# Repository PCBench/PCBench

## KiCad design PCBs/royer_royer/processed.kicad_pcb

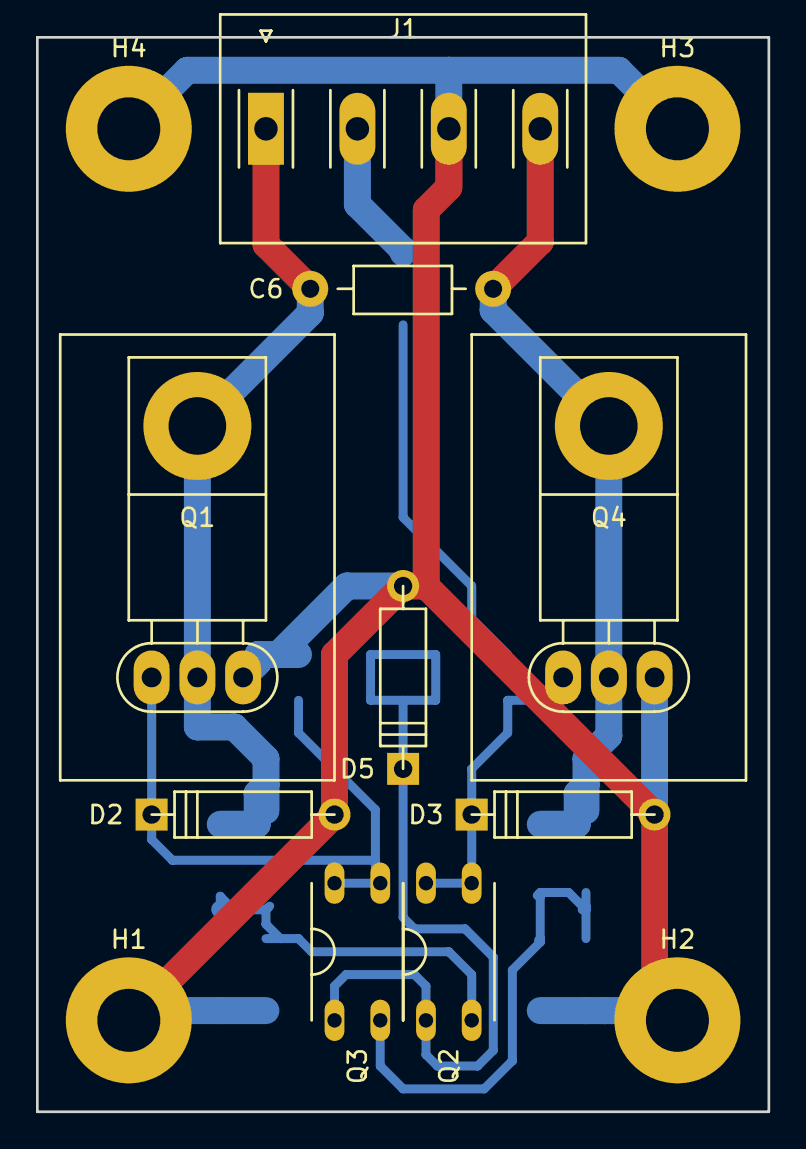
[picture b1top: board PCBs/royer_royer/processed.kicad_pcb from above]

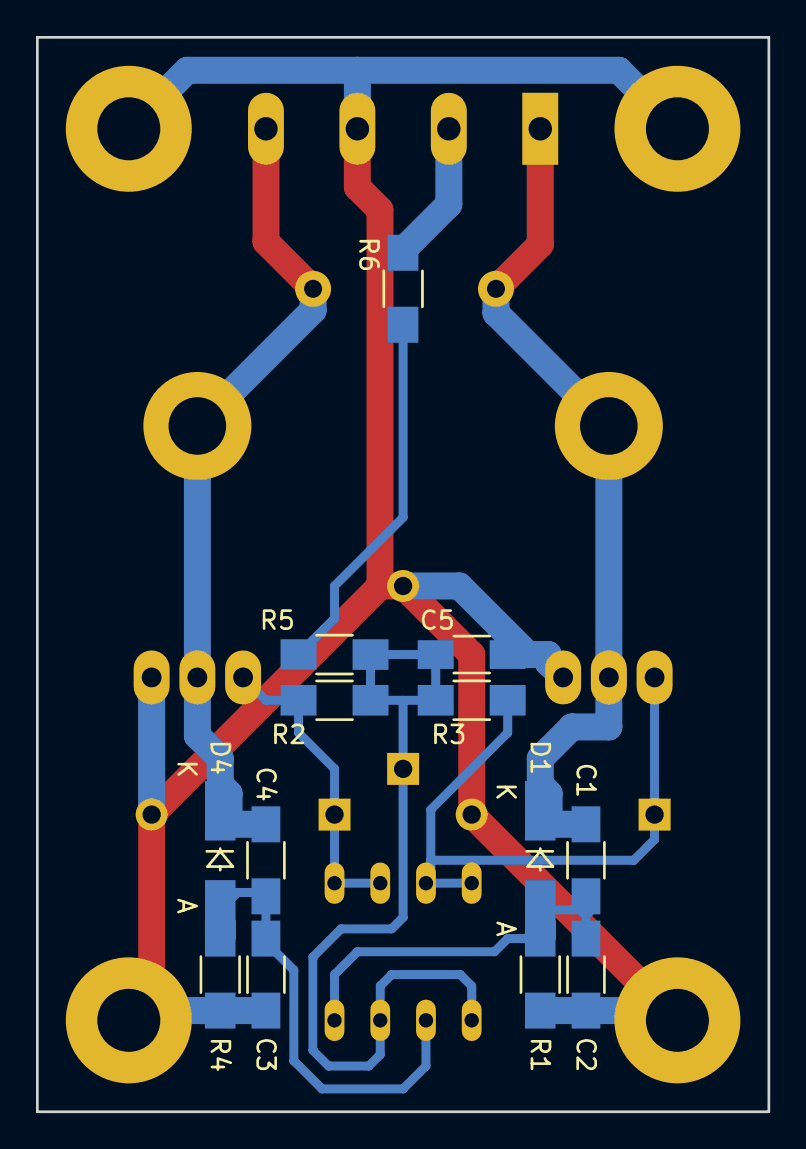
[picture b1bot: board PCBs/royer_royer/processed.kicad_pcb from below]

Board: 2 copper layers, 40.6 x 59.7 mm, 26 parts (13 on the bottom side), 10 nets.

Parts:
C1, C2, C3, C4: 10nF; C_1206_HandSoldering
C5: 470nF; C_1206_HandSoldering
C6: 1uF; Choke_Horizontal_RM10mm
D1, D4: 1N4148; MiniMELF_Handsoldering
D2, D3, D5: 9.1V; D4
H1, H2, H3, H4: 3.5mm; MountingHole_3.5mm_Pad
J1: Screw_Terminal_1x04; screw-terminal-4-pin
Q1, Q4: IRFB4410; TO-220-small-heatsink
Q2, Q3: IRFD110; DIP-4_W7.62mm_LongPads
R1, R4: 33k; R_1206_HandSoldering
R2, R3: 47k; R_1206_HandSoldering
R5, R6: 1k; R_1206_HandSoldering

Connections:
/9V: C5.1, D5.1, Q2.1, Q3.1, R2.1, R3.1, R5.2
/24V: J1.2, R6.1
/C1: C1.2, C6.2, D1.1, J1.1, Q1.2
/C2: C4.2, C6.1, D4.1, J1.4, Q4.2
/D1: C1.1, C2.1, D1.2, Q2.2, R1.1
/D2: C3.1, C4.1, D4.2, Q3.2, R4.1
/G1: D2.1, Q1.1, Q3.3, R3.2
/G2: D3.1, Q2.3, Q4.1, R2.2
GND: C2.2, C3.2, C5.2, D2.2, D3.2, D5.2, H1.1, H2.1, H3.1, H4.1, J1.3, Q1.3, Q4.3, R1.2, R4.2
unnamed: R5.1, R6.2

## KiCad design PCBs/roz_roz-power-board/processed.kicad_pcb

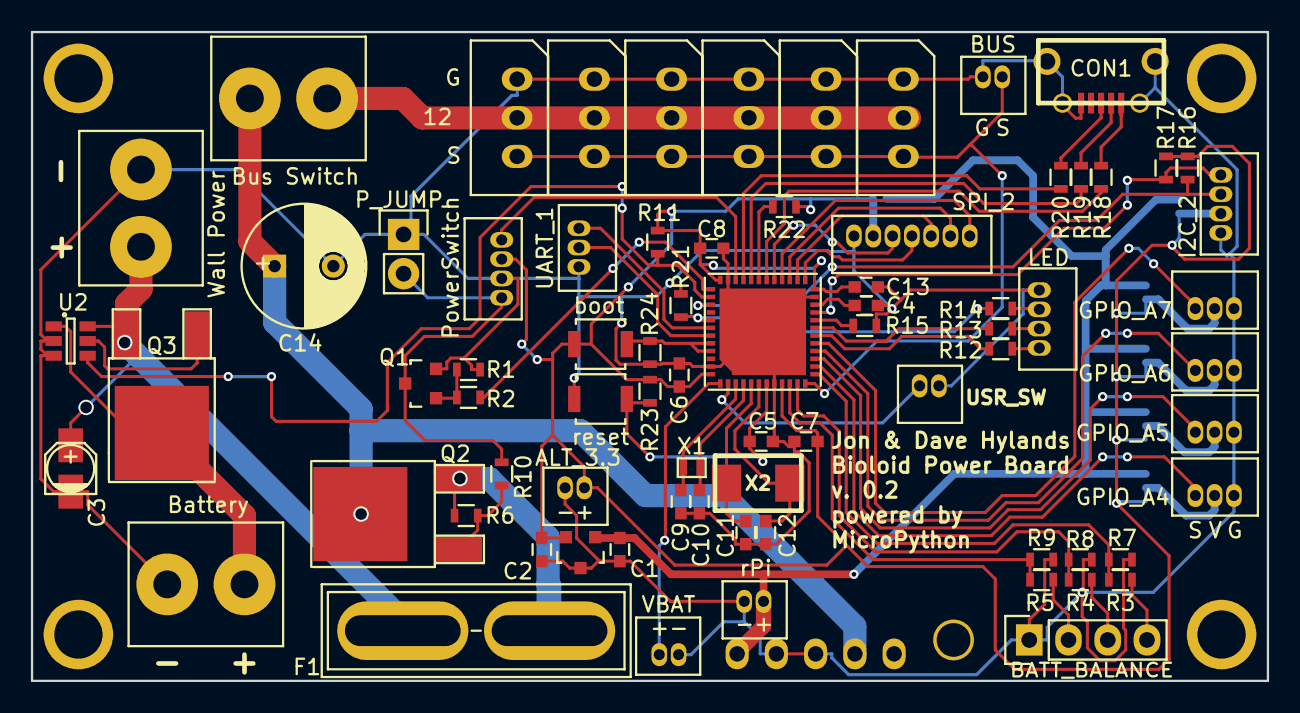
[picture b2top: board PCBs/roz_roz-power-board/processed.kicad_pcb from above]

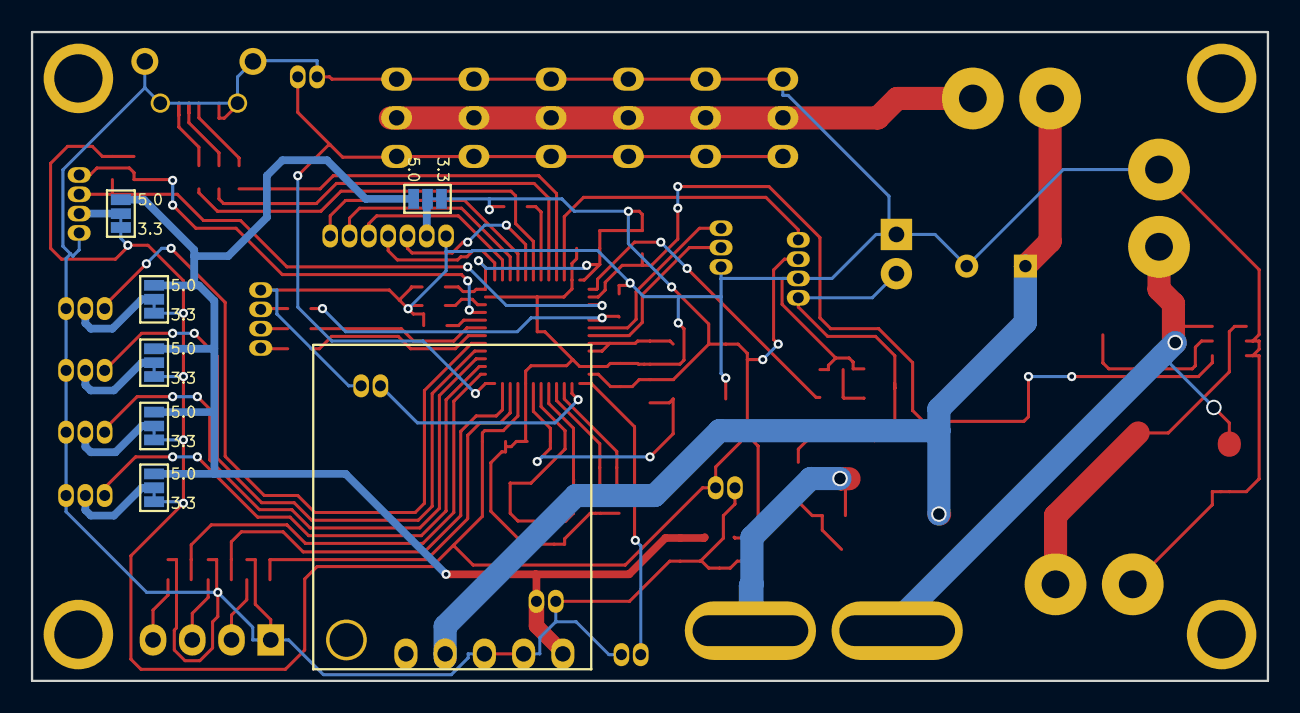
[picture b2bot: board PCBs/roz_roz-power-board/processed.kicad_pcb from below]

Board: 2 copper layers, 80.0 x 42.0 mm, 87 parts (7 on the bottom side), 64 nets.

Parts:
1PIN: P***; 2_56_hole
1PIN_2, 1PIN_3, 1PIN_4, 1PIN_5: P***; 4_40_hole
C1, C2, C4, C5, C6, C7, C8, C13: 0.1uF; C_0603
C3: 22uF; c_elec_3x5.3
C9, C10: 6pF; C_0603
C11, C12: 18pF; C_0603
C14: 680uF; C_Radial_D8_L21_P3.8
CON1: USB-MICRO-B; USB_MICRO_B
F1: FUSE; BladeFuse-CarType
J1, J2, J3, J4, J5, J6: Jumper_Switch; Jumper-Switch
P1: Wall Power; TerminalBlock
P2: Battery; TerminalBlock
P3: BATT_BALANCE; Socket_Strip_Straight_1x04
P4: ALT_3.3; SIL_2_050
P5: UART_1; SIL_3_050
P6: I2C_2; SIL_4_050
P7: SPI_2; SIL_7_050
P8: 5V Regulator; 5V_5A_VReg
P9: GPIO_A4; SIL_3_050
P10: GPIO_A5; SIL_3_050
P11: GPIO_A6; SIL_3_050
P12: GPIO_A7; SIL_3_050
P13: BIOLOID_BUS_1; Bioloid-3
P14: LED; SIL_4_050
P15: Bus Switch; TerminalBlock
P16: BIOLOID_BUS_2; Bioloid-3
P17: BIOLOID_BUS_3; Bioloid-3
P18: BIOLOID_BUS_4; Bioloid-3
P19: BIOLOID_BUS_5; Bioloid-3
P20: BIOLOID_BUS_6; Bioloid-3
P21: rPi; SIL_2_050
P23: USR_SW; SIL_2_050
P25: VBAT; SIL_2_050
P26: BUS; SIL_2_050
P_JUMP: P_JUMP; Socket_Strip_Straight_1x02
Q1: BS-170; SOT-23
Q2, Q3: STD30PF03LT4; TO-252-2Lead
R1, R10, R15, R21, R23: 10K; R_0603
R2: 100; R_0603
R3, R4, R5: 15K; R_0603
R6: 22K; R_0603
R7, R8, R9: 5K; R_0603
R11: 470K; R_0603
R12: 65; R_0603
R13: 0; R_0603
R14: 5; R_0603
R16, R17: 4.7K; R_0603
R18: 1K; R_0603
R19, R20: 20; R_0603
R22, R24: 100K; R_0603
SW2: PowerSwitch; SIL_4_050
SW3: RESET_SW; PUSH_SMT
SW4: BOOT_SW; PUSH_SMT
U1: AP7333; SOT-23
U2: LTC4412; SOT-23-6
U3: STM32F401xD_UFQFPN48; UFQFPN48
X1: 32.768kHz; CRYSTAL_SMT_3
X2: 8MHz; CRYSTAL_SMT

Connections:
+3V3: C2.1, C6.2, C7.2, C8.2, C13.2, J1.3, J2.3, J3.3, J4.3, J5.3, J6.3, P4.1, R11.2, R16.2, R17.2, R22.2, R23.1, SW2.3, SW4.2, U1.2, U3.9, U3.24, U3.36, U3.48
+5V: C1.1, J1.1, J2.1, J3.1, J4.1, J5.1, J6.1, P8.5, P21.1, U1.1
+12V: C14.1, P8.2, P15.2, Q2.2
+BATT: P2.2, Q3.2, U2.1
+F_POWER: F1.2, Q2.3, R6.2
+POWER: C3.1, F1.1, P1.2, Q3.3, U2.6
+SW_12V: P13.2, P15.1, P16.2, P17.2, P18.2, P19.2, P20.2
/OSC32_IN: C9.2, U3.3, X1.2
/OSC32_OUT: C10.2, U3.4, X1.1
/OSC_IN: C11.2, U3.5, X2.2
/OSC_OUT: C12.2, U3.6, X2.1
BIOLOID_TX: P13.1, P16.1, P17.1, P18.1, P19.1, P20.1, P26.1, U3.12
BOOT0: R24.2, SW4.1, U3.44, U3.45
CELL1_VOLTAGE: R5.1, R9.2, U3.10
CELL2_VOLTAGE: R4.1, R8.2, U3.11
CELL3_VOLTAGE: R3.1, R7.2, U3.13
GATE_PIN: R2.2, U3.37
GND: C1.2, C2.2, C3.2, C4.1, C5.1, C6.1, C7.1, C8.1, C9.1, C10.1, C11.1, C12.1, C13.1, C14.2, CON1.5, CON1.6, CON1.7, CON1.8, CON1.9, P1.1, P2.1, P3.1, P4.2, P5.3, P6.4, P7.7, P8.3, P8.4, P9.3, P10.3, P11.3, P12.3, P13.3, P14.1, P16.3, P17.3, P18.3, P19.3, P20.3, P21.2, P23.1, P25.2, P26.2, P_JUMP.1, Q1.2, R1.1, R7.1, R8.1, R9.1, R15.2, R21.2, R24.1, SW2.2, SW3.2, U1.3, U2.2, U2.3, U3.8, U3.23, U3.35, U3.47, U3.G1, U3.G2, U3.G3
GPIO_A4: P9.1, U3.14
GPIO_A5: P10.1, U3.15
GPIO_A6: P11.1, U3.16
GPIO_A7: P12.1, U3.17
I2C_2_SCL: P6.1, R17.1, U3.21
I2C_2_SDA: P6.2, R16.1, U3.39
LED_B: R14.1, R21.1, U3.41
LED_G: R13.1, U3.19
LED_R: R12.1, U3.18
unnamed: C4.2, U3.22
unnamed: C5.2, R23.2, SW3.1, U3.7
unnamed: CON1.1, R18.2
unnamed: CON1.2, R19.2
unnamed: CON1.3, R20.2
unnamed: J1.2, P6.3
unnamed: J2.2, P7.6
unnamed: J3.2, P9.2
unnamed: J4.2, P10.2
unnamed: J5.2, P11.2
unnamed: J6.2, P12.2
unnamed: P3.2, R5.2
unnamed: P3.3, R4.2
unnamed: P3.4, R3.2
unnamed: P14.2, R14.2
unnamed: P14.3, R13.2
unnamed: P14.4, R12.2
unnamed: P_JUMP.2, Q1.3, R10.1, SW2.1
unnamed: P23.2, U3.2
unnamed: Q1.1, R1.2, R2.1
unnamed: Q2.1, R6.1, R10.2
unnamed: Q3.1, U2.5
unnamed: R19.1, U3.32
unnamed: R20.1, U3.33
PA9: R18.1, U3.30
PA10: R22.1, U3.31
PB2: R15.1, U3.20
SPI_2_MISO: P7.2, U3.27
SPI_2_MOSI: P7.1, U3.28
SPI_2_SCK: P7.3, U3.26
SPI_CS_1: P7.4, U3.25
SPI_CS_2: P7.5, U3.29
STAT_PIN: R11.1, U2.4, U3.38
SWITCH_PIN: SW2.4, U3.34
UART_1_RX: P5.2, U3.43
UART_1_TX: P5.1, U3.42
VBAT: P25.1, U3.1

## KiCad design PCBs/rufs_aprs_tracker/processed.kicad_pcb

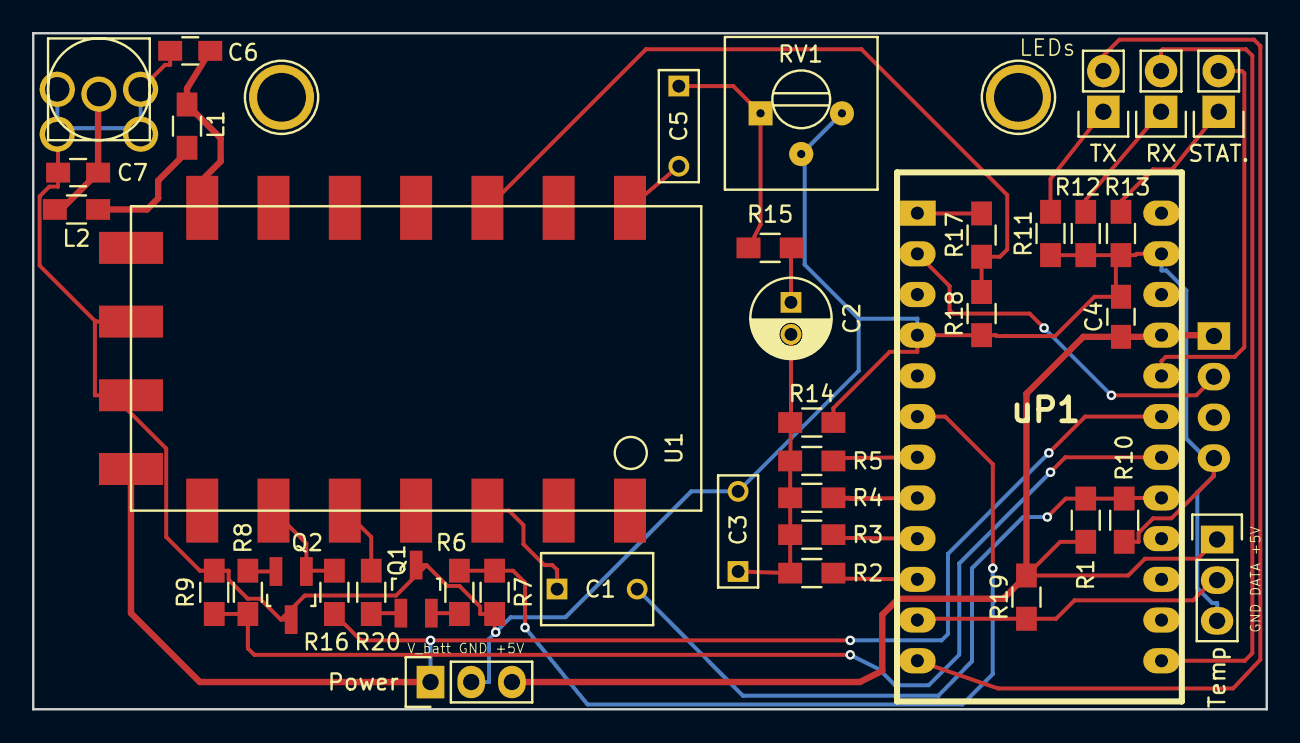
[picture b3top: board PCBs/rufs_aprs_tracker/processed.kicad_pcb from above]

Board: 2 copper layers, 77.0 x 42.2 mm, 41 parts (1 on the bottom side), 33 nets.

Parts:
C1: 1uF; C_Rect_L7_W4.5_P5
C2: 4.7uF; C_Radial_D5_L11_P2
C3, C5: 100nF; C_Rect_L7_W2.5_P5
C4: 100nF; C_0805_HandSoldering
C6, C7: 15pF; C_0805_HandSoldering
J1: SMA; sma_female_top
L1, L2: 0.027uH; R_0805_HandSoldering
P3: GPS; ublox_gps_breakout
Power: POWER; Pin_Header_Straight_1x03
Q1, Q2: 2N7002; SOT-23_Handsoldering
R1, R10, R15: 100K; R_0805_HandSoldering
R2: 1K 1%; R_0805_HandSoldering
R3: 2K2 1%; R_0805_HandSoldering
R4: 3K9 1%; R_0805_HandSoldering
R5: 8K2 1%; R_0805_HandSoldering
R6, R7, R8, R9: 1K; R_0805_HandSoldering
R11, R12, R13: 3K3; R_0805_HandSoldering
R14: 270 1%; R_0805_HandSoldering
R16, R17, R20: 10K; R_0805_HandSoldering
R18: 20K; R_0805_HandSoldering
R19: 4.7K; R_0805_HandSoldering
RV1: 10K; Potentiometer_Trimmer-Suntan-TSR-3386P
RX: RX (RED); Pin_Header_Straight_1x02
STAT.: STATUS (GREEN); Pin_Header_Straight_1x02
TX: TX (GREEN); Pin_Header_Straight_1x02
Temp: TEMPERATURE; Pin_Header_Straight_1x03
U1: DRA818V; dra818v
uP1: Pro Mini 5V 16MHz; ARDUINO_PRO_MINI

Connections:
+5V: C4.1, P3.1, Power.3, R1.2, R19.1, Temp.1, uP1.21
/AUDIO_IN: C1.2, R1.1, R10.1, uP1.17
/D4: R5.2, uP1.7
/D5: R4.2, uP1.8
/D6: R3.2, uP1.9
/D7: R2.2, uP1.10
/D9: TX.2, uP1.12
/D10: RX.2, uP1.13
/GPS_RX: P3.2, uP1.2
/LINE_LEVEL_IN: C1.1, U1.3
/MIC_LEVEL_OUT: C5.1, R15.1, RV1.1
/PTT_CONTROL: R6.2, R7.2, uP1.6
/PTT_V+: Q1.1, R20.2
/RADIO_PD: Q2.1, R16.2, U1.6
/RADIO_PD_CONTROL: R8.2, R9.2, uP1.18
/RADIO_TX: R17.1, R18.1, U1.16
/STATUS_LED: STAT..2, uP1.20
/TEMP_DATA: R19.2, Temp.2, uP1.11
/V_BATT: Power.1, R16.1, U1.8, uP1.19
GND: C3.2, C4.2, C6.2, C7.2, J1.2, J1.3, J1.4, J1.5, P3.4, Power.2, Q1.3, Q2.3, R7.1, R9.1, R10.2, R11.1, R12.1, R13.1, R14.2, R18.2, RV1.2, RV1.3, Temp.3, U1.9, U1.10, uP1.4, uP1.23
unnamed: C2.1, R15.2
unnamed: C2.2, C3.1, R2.1, R3.1, R4.1, R5.1, R14.1
unnamed: C5.2, U1.18
unnamed: C6.1, L1.1, U1.12
unnamed: C7.1, J1.1, L2.2
unnamed: R11.2, TX.1
unnamed: R12.2, RX.1
unnamed: R13.2, STAT..1
unnamed: L1.2, L2.1
unnamed: Q1.2, R6.1
unnamed: Q2.2, R8.1
unnamed: R17.2, uP1.1
unnamed: R20.1, U1.5

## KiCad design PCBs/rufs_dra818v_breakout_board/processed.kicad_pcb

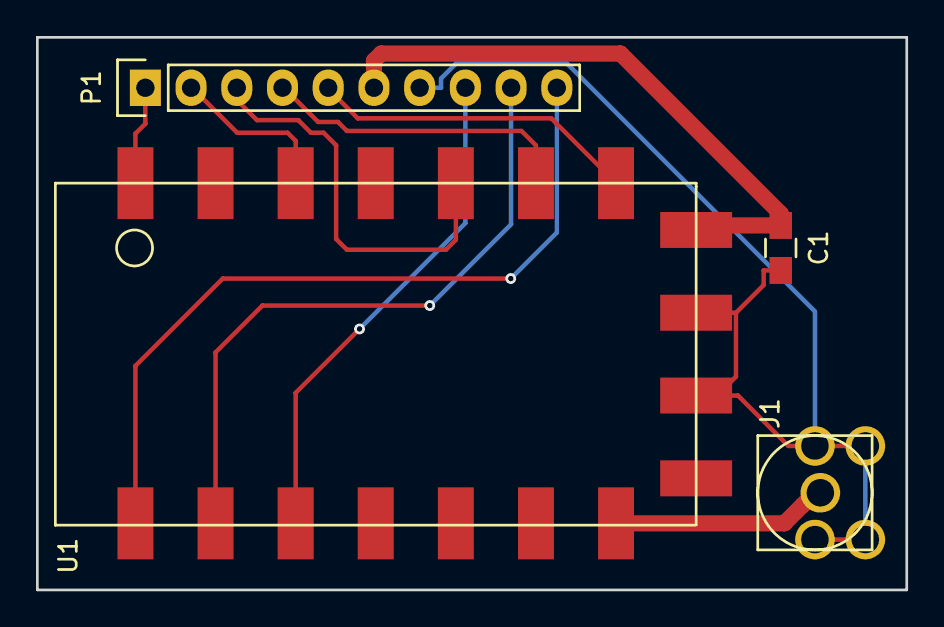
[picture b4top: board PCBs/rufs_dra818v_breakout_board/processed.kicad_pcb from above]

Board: 2 copper layers, 48.3 x 30.7 mm, 4 parts (0 on the bottom side), 11 nets.

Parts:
C1: 100nF X7R; C_0805_HandSoldering
J1: SMA female; sma_female_top
P1: CONN_01X10; Pin_Header_Straight_1x10
U1: DRA818V; dra818v

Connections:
GND: C1.2, J1.2, J1.3, J1.4, J1.5, P1.7, U1.9, U1.10
unnamed: J1.1, U1.12
unnamed: P1.1, U1.1
unnamed: P1.2, U1.3
unnamed: P1.3, U1.5
unnamed: P1.4, U1.6
unnamed: P1.5, U1.7
unnamed: P1.8, U1.16
unnamed: P1.9, U1.17
unnamed: P1.10, U1.18
VCC: C1.1, P1.6, U1.8

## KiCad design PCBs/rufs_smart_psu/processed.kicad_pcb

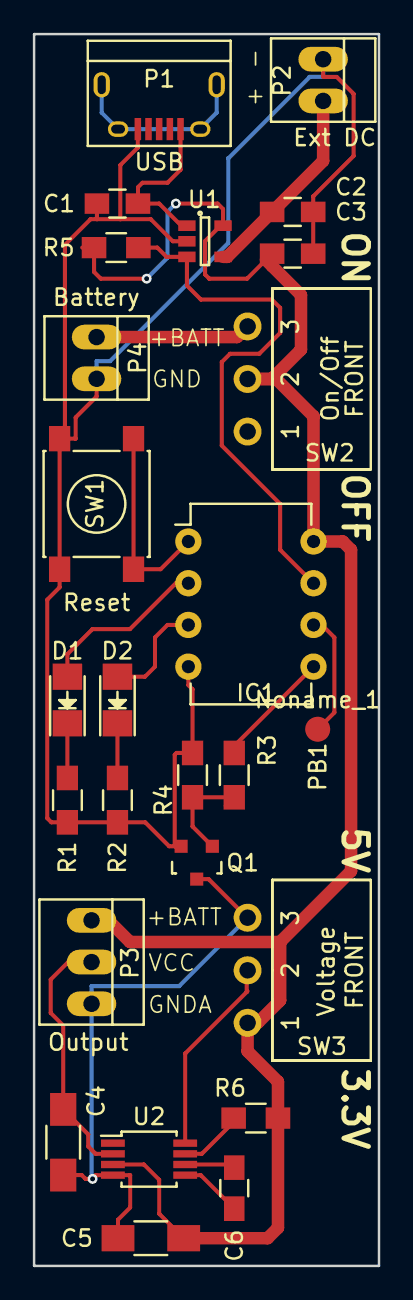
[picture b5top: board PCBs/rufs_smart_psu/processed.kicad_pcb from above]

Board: 2 copper layers, 21.0 x 75.0 mm, 26 parts (0 on the bottom side), 20 nets.

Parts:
C1, C2, C3, C6: C_0805_HandSoldering
C4, C5: C_1206_HandSoldering
D1, D2: LED_1206
IC1: DIP-8_W7.62mm
Noname_1: PB1; Measurement_Point_Round-SMD-Pad_Small
P1: USB; USB_Micro-B
P2: Ext DC; PINHEAD1-2
P3: Output; PINHEAD1-3
P4: Battery; PINHEAD1-2
Q1: SOT-23
R1, R2, R3, R4, R5, R6: R_0805_HandSoldering
SW1: Reset; SW_SPST_PTS645
SW2: On/Off; spdt_slide_switch_angled
SW3: Voltage; spdt_slide_switch_angled
U1: SOT-23-5
U2: MSOP-8_3x3mm_Pitch0.65mm

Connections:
+BATT: C3.1, C5.1, IC1.8, P3.1, R5.2, R6.2, SW2.2, SW3.1, U1.5, U2.3
GND: C1.1, C2.2, C3.2, IC1.4, P1.5, P2.1, P4.2, Q1.3, R1.2, R2.2, R4.2, SW1.1, U1.2
GNDA: C4.2, C5.2, P3.3, Q1.1, SW3.3, U2.4
unnamed: C1.2, P1.1, U1.1
unnamed: C2.1, P2.2, U1.4
unnamed: C6.1, U2.6
unnamed: C6.2, U2.5
unnamed: D1.1, R1.1
unnamed: D1.2, IC1.2
unnamed: D2.1, R2.1
unnamed: D2.2, IC1.3
unnamed: IC1.1, SW1.2
unnamed: IC1.5, R3.2
unnamed: IC1.6, Noname_1.1
unnamed: IC1.7, R5.1, U1.3
unnamed: P4.1, SW2.3
unnamed: Q1.2, R3.1, R4.1
unnamed: R6.1, U2.7
unnamed: SW3.2, U2.8
VCC: C4.1, P3.2, U2.2

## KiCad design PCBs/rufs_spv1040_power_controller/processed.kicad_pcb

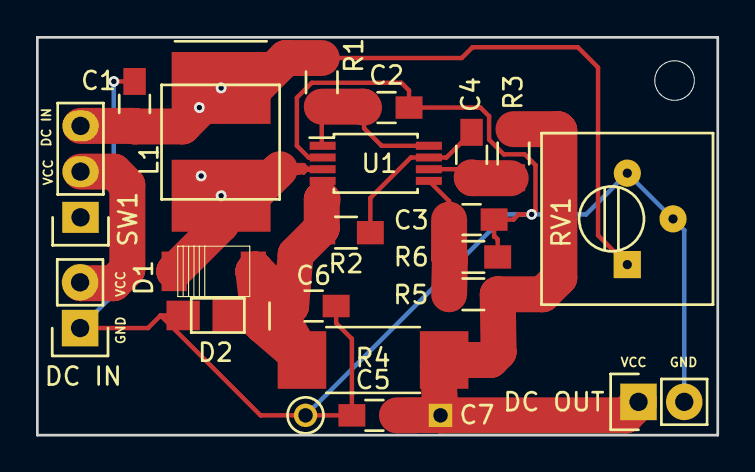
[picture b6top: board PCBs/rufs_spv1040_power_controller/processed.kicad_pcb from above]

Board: 2 copper layers, 37.8 x 22.1 mm, 21 parts (0 on the bottom side), 10 nets.

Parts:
C1, C2, C5, C6: 10uF; C_0805_HandSoldering
C3: 1nF; C_0805_HandSoldering
C4: 1uF; C_0805_HandSoldering
C7: 4700uF; C_Radial_D16_L25_P7.5
D1: D_Schottky; SOD-128
D2: TVS; STmite_flat_DO216-AA
DC IN: DC IN; Pin_Header_Straight_1x02
DC OUT: DC OUT; Pin_Header_Straight_1x02
L1: 10uH; XAL6060
R1, R2, R3: 1K; R_0805_HandSoldering
R4: 10m; R_2512_HandSoldering
R5: 1M; R_0805_HandSoldering
R6: 330K; R_0805_HandSoldering
RV1: POT; Potentiometer_Trimmer-Suntan-TSR-3386P
SW1: SWITCH_INV; Pin_Header_Straight_1x03
U1: SPV1040; TSSOP-8_4.4x3mm_Pitch0.65mm

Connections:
GND: C1.2, C2.2, C3.2, C5.2, C6.2, C7.2, D2.1, DC IN.1, DC OUT.2, R6.2, RV1.2, RV1.3, U1.2
unnamed: C1.1, L1.2, R1.1, RV1.1, SW1.3
unnamed: C2.1, R1.2, U1.1, U1.8
unnamed: C3.1, R5.2, R6.1, U1.5
unnamed: C4.1, R2.2, U1.7
unnamed: C4.2, R3.2, U1.6
unnamed: C5.1, C7.1, DC OUT.1, R3.1, R4.1, R5.1
unnamed: C6.1, D1.1, D2.2, R2.1, R4.2, U1.4
unnamed: D1.2, L1.1, U1.3
VCC: DC IN.2, SW1.2

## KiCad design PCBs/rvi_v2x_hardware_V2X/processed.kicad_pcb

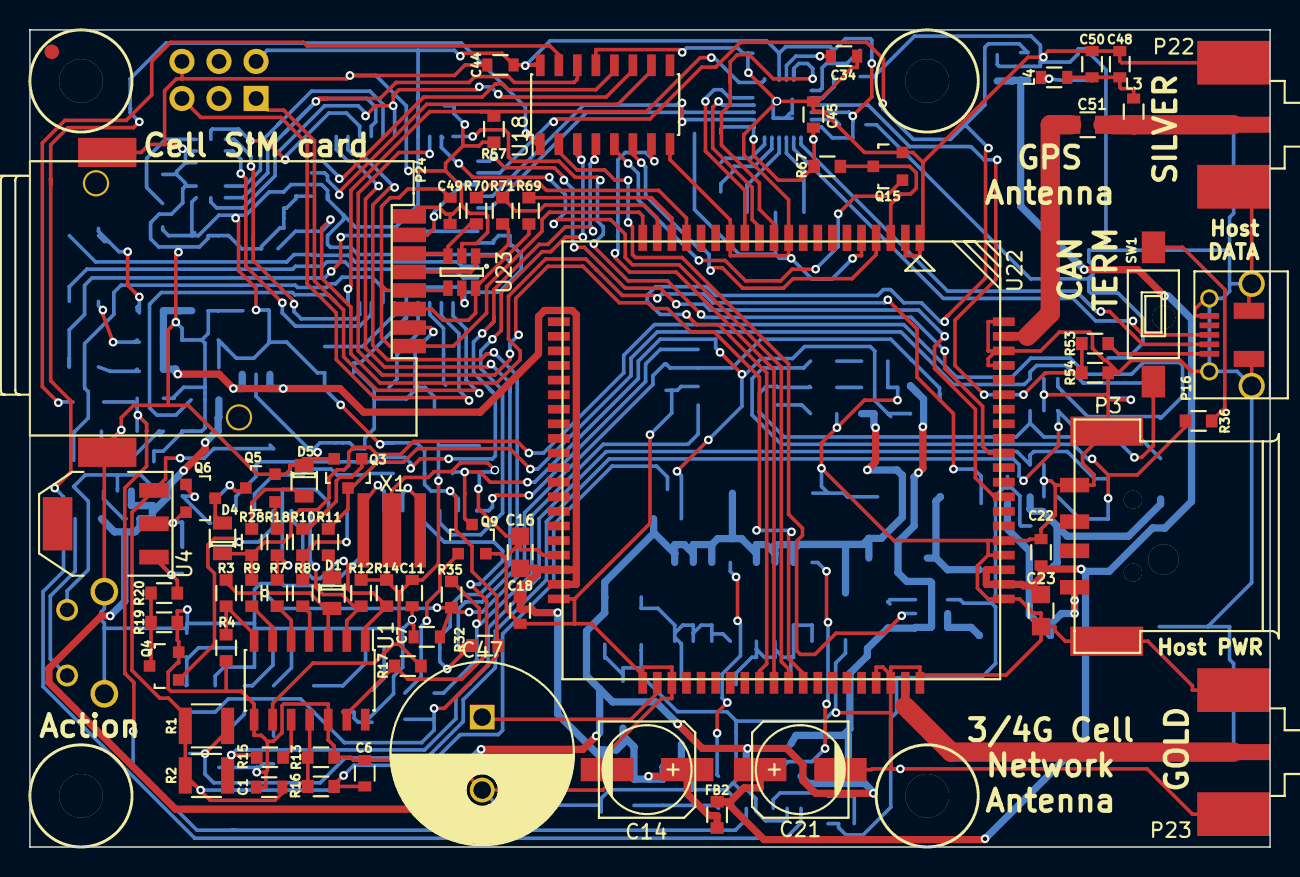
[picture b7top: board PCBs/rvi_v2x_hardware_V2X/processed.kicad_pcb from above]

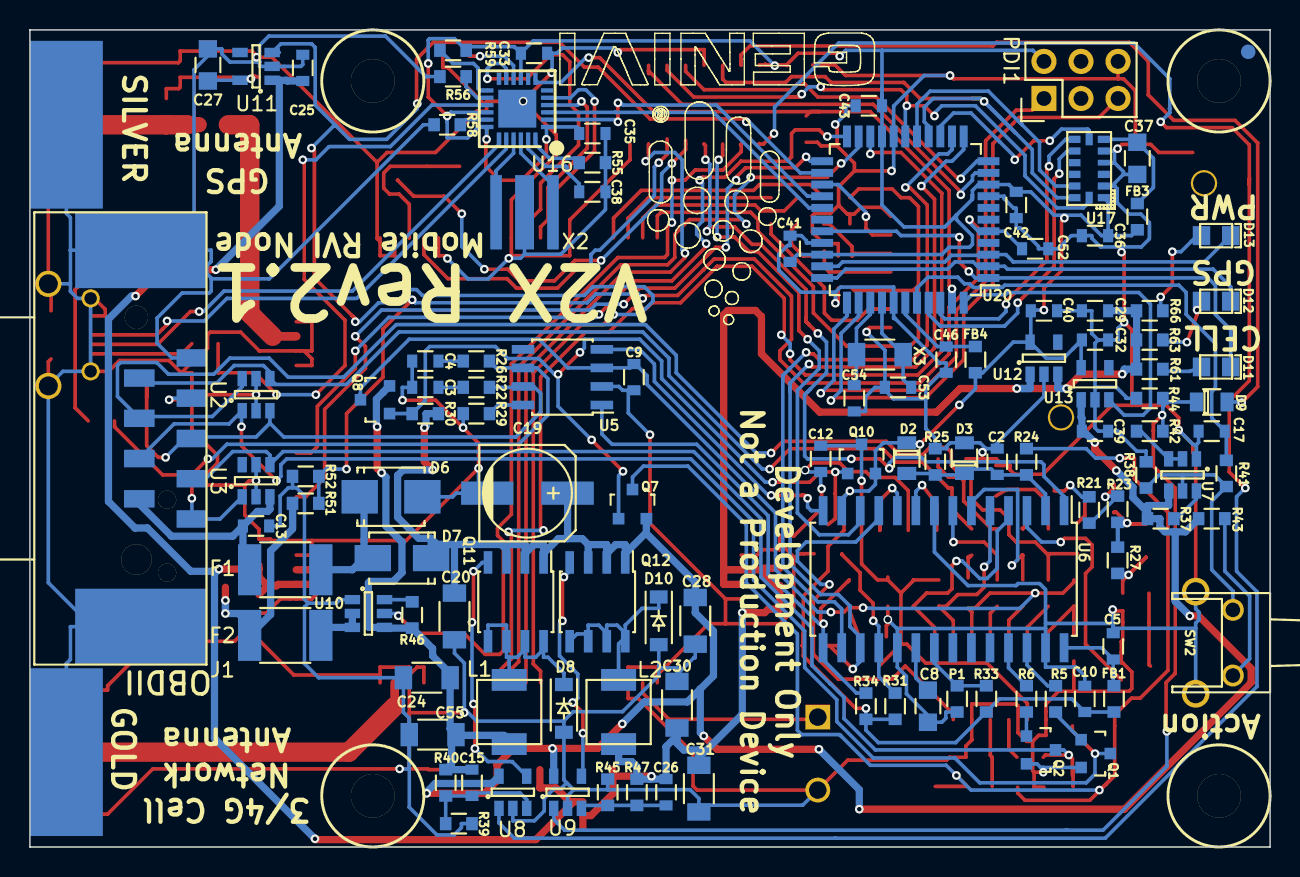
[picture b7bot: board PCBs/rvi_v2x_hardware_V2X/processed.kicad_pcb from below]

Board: 2 copper layers, 85.0 x 56.0 mm, 192 parts (115 on the bottom side), 142 nets.

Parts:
C1, C2, C6, C7, C12, C18, C25, C29, C32, C33, C36, C38, C39, C40, C41, C42, C43, C44, C45, C49, C52: 100N; C_0603_SM
C3, C4: 560P; C_0603_SM
C5, C9, C10, C11, C34, C35, C46: 1U; C_0603_SM
C8, C16, C23, C27, C37: 4U7; C_0805_SM
C13, C17, C22: 10N; C_0603_SM
C14, C21: 220U; c_elec_6.3x5.8
C15: 220P; C_0603_SM
C19: 100U; c_elec_6.3x5.8
C20, C28: 4U7; C_1206_SM
C24, C30, C31, C55: 10U; C_1206_SM
C26: 330P; C_0603_SM
C47: 0.1F; C_Radial_D12.5_L25_P5
C48: 56P; C_0603_SM
C50: 470P; C_0603_SM
C51: 150p; C_0805_SM
C53, C54: 9p; C_0603_SM
D1, D2, D3, D4, D5, D9: 4148; Diode_0805_12_SM
D6: SMBJ16A; SMB_Standard
D7: B320A-13-F; SMA_Standard
D8, D10: SBR3U30P1-7; SOD-123
D11: GREEN; 0805_LED
D12: BLUE; 0805_LED
D13: RED; 0805_LED
F1: 1.25A; R_1812
F2: 2A; R_1812
FB1, FB2, FB3, FB4: 220; R_0603_sm
J1: DB9; DB-9_SMT
L1, L2: 5U6; L_4.5x4.5
L3: 120N; L_0603_SM
L4: 330N; L_0603_SM
P1: NVM_RST; R_0603_sm
P3: USB_A; USB-A-SMT
P4: Board Mount 1; MountingHole_3mm
P5: Board Mount 2; MountingHole_3mm
P6: Board Mount 3; MountingHole_3mm
P7: Board Mount 4; MountingHole_3mm
P9: Ficudial2; Fiducial_1mm_Dia_2.54mm_Outer_CopperTop
P13: Ficudial2; Fiducial_1mm_Dia_2.54mm_Outer_CopperBottom
P16: USB_u; USB_Micro-B-DX4R005JJ2R1800
P22, P23: SMA; SMA-RA_142-0701-801
P24: SIM_SKT; 47553-1001
PDI1: AVR-PDI-6; Pin_Header_Straight_2x03
Q1, Q2, Q3, Q5: 2N3904; SOT_23_123
Q4, Q9, Q15: 2N7000; SOT_23_123
Q6: 3906; SOT_23_123
Q7, Q8, Q10: BSS84; SOT_23_123
Q11, Q12: IRF9335; SOIC-8_MOS
R1, R2: 510; R_1210_SM
R3, R21: 2K2; R_0603_sm
R4: 8.87K; R_0603_sm
R5, R6, R10, R32, R35: 1K; R_0603_sm
R7, R8, R9, R11, R12, R13, R14, R15, R16, R17, R18, R23, R25, R28, R30, R31, R37, R41, R46, R67: 10K; R_0603_sm
R19: 374; R_0603_sm
R20: 866; R_0603_sm
R22, R26, R36: 120; R_0603_sm
R24: 62K; R_0603_sm
R27: 240; R_0603_sm
R29: 4.7K; R_0603_sm
R33, R34: 100K; R_0603_sm
R38, R44: 24K; R_0603_sm
R39, R45: 2K0; R_0603_sm
R40: 10K5; R_0603_sm
R42, R43, R51, R52, R53, R54, R56, R57, R58, R59: 47K; R_0603_sm
R47: 8K2; R_0603_sm
R55: 12K; R_0603_sm
R61, R66: 330; R_0603_sm
R63: 220; R_0603_sm
R69, R70, R71: 22; R_0603_sm
SW1: SPST; SW_SPST_FSMSM_SM
SW2: SW_PUSH; PTS645VK58-2-LFS
U1: LM339; SOIC-14_3.9x8.7mm_Pitch1.27mm
U2, U3: ESDAxxSC6; SOT-23-6
U4: LM317; SOT-223
U5: MCP2551; SOIC-8_3.9x4.9mm_Pitch1.27mm
U6: STN1110; SOIC-28_7.5x17.9mm_Pitch1.27mm
U7, U10: FDC6326L; SOT-23-6
U8, U9: XRP6124; SOT-23-5
U11, U12, U13: TLV70012DCK; SOT-23-5
U16: USB2422; QFN-24-USB2422
U17: ADXL345; LGA-14_5x3mm
U18: 74HC595; SOIC-16_3.9x9.9mm_Pitch1.27mm
U20: ATXMEGA128A4U-AU; TQFP-44_10x10mm_Pitch0.8mm
U22: SIM5320
U23: MMQA5V6T3G; SOT-23-6
X1: 16MHz; AWSCR
X2: 24MHz; AWSCR
X3: 32.768K; C_1206_SM

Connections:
3V3: C10.1, C32.1, C33.1, C35.1, C36.1, C40.1, C41.1, C42.1, C43.1, C44.1, C45.1, D2.1, FB1.1, FB3.1, FB4.1, PDI1.2, Q10.2, R31.1, R32.1, R33.1, R34.1, R59.2, R67.2, U6.13, U12.5, U13.5, U16.1, U16.9, U16.16, U16.18, U17.1, U18.16, U20.9, U20.19, U20.31
3V3F1: C27.1, L4.1, U11.5
3V3_EN: U13.3, U20.44
3V3_F: C46.1, FB4.2, U20.39
4V1: C14.1, C16.1, C18.1, C26.1, C29.1, C30.1, C31.1, FB2.2, L2.2, R47.1, R61.2, R63.2, R66.2, U12.1, U12.3, U22.38, U22.39
4V1F1: C21.1, C22.1, C23.1, C25.1, FB2.1, U11.1, U22.62, U22.63
4V1_EN: D9.2, U18.15
5V0_A: C15.1, C24.1, C55.1, L1.2, Q8.2, R40.2, R46.1, U10.4
5V0_B: F2.1, U10.2, U10.3
5V0_B_EN: U10.5, U18.2
5V0_B_OUT: F2.2, P3.1, R51.2
5V0_EN: U8.1, U18.1
5V0_HOST: P16.1, R53.1
12V0_A: C13.1, F1.1, J1.9, U3.3
12V0_B: C19.1, C20.1, C28.1, C39.1, D7.1, Q7.2, Q11.2, Q12.2, R30.1, R37.2, R43.1, U7.4, U8.5, U9.5, U13.1
ACL_INT1: U17.8, U20.42
ACL_INT2: U17.9, U20.41
BAT_SAMPLE: C2.1, D2.2, D3.1, R24.2, R25.1, U6.2
BUTTON: C17.1, R41.2, U20.40
CAN_3.3V_SW: C11.1, C12.1, Q10.3, R12.1, R14.1, R17.1, U1.9
CAN_5V_SW: C7.1, C9.1, D1.2, Q8.3, R3.1, R35.1, U1.3, U5.3
CAN_12V_SW: C1.1, C6.1, Q7.3, R1.2, R2.2, R16.1, R24.1, U4.3
CAN_CLK: U6.9, X1.1
CAN_CLKN: U6.10, X1.2
CAN_H: J1.3, R22.1, SW1.1, U2.3, U5.7
CAN_L: J1.5, R26.1, R36.1, U3.1, U5.6
CAN_POWERDOWN: Q9.1, R31.2, U6.18
CAN_RX: U5.4, U6.14
CAN_RXD: U6.16, U20.13
CAN_TX: R34.2, R35.2, U5.1, U6.15
CAN_TXD: R32.2, U6.17, U20.12
GND: C1.2, C2.2, C3.2, C4.2, C5.2, C6.2, C7.2, C8.2, C9.2, C10.2, C11.2, C12.2, C13.2, C14.2, C16.2, C17.2, C18.2, C19.2, C20.2, C21.2, C22.2, C23.2, C24.2, C25.2, C27.2, C28.2, C29.2, C30.2, C31.2, C32.2, C33.2, C34.2, C35.2, C36.2, C37.2, C38.2, C39.2, C40.2, C41.2, C42.2, C43.2, C44.2, C45.2, C46.2, C47.2, C48.2, C49.2, C50.2, C52.2, C53.1, C54.1, C55.2, D3.2, D5.1, D6.2, D8.2, D10.2, J1.1, J1.2, J1.M, P1.2, P3.4, P3.5, P16.5, P16.6, P22.2, P23.2, P24.A, P24.B, P24.C5, P24.SW2, PDI1.6, Q1.2, Q2.2, Q3.2, Q4.2, Q5.2, Q9.2, Q15.2, R4.1, R13.2, R19.1, R25.2, R29.2, R38.1, R39.1, R44.1, R45.1, R52.1, R54.2, R55.1, R56.2, R57.2, R58.1, SW2.S, U1.8, U1.12, U2.2, U2.5, U3.2, U3.5, U5.2, U6.8, U6.19, U6.27, U7.1, U8.2, U9.2, U10.1, U11.2, U12.2, U13.2, U16.25, U17.2, U17.4, U17.5, U18.8, U18.13, U20.8, U20.18, U20.30, U20.38, U22.1, U22.2, U22.5, U22.10, U22.14, U22.37, U22.40, U22.41, U22.43, U22.57, U22.58, U22.60, U22.61, U22.64, U22.65, U22.77, U22.78, U22.80, U23.2, U23.5, X1.3, X2.3
GPS: C51.1, L3.1, P22.1
GPS_ANT: C51.2, U22.79
GPS_EN: U11.3, U20.24, U22.49
GSM_ANT: P23.1, U22.59
HOST_SC: C52.1, R51.1, R52.2, U20.5
HUB_CLK: U16.22, X2.2
HUB_CLKN: U16.21, X2.1
HUB_DM: P16.2, U16.19
HUB_DP: P16.3, U16.20
HUB_PWR_PRT1: R57.1, U16.7, U20.43
HUB_PWR_PRT2: U16.11, U22.11
HUB_SCL: R56.1, U16.14
HUB_SDA: R59.1, U16.13
HUB_SUSP_IND: R58.2, U16.17
ISO_K_TX: R6.1, U6.25
ISO_L_TX: R5.1, U6.26
ISO_RX: R17.2, U1.13, U6.11
J1850+: D4.1, J1.7, R9.2, R28.1, U2.6
J1850-: J1.6, Q3.3, R11.2, U2.4
J1850_BUS_+_TX: R7.2, R18.2, U6.6
J1850_BUS_-_TX: R8.2, R10.2, U6.7
K-LINE: J1.4, Q2.3, R2.1, R15.2, U3.4
L-LINE: J1.8, Q1.3, R1.1, U2.1
unnamed: C3.1, R22.2
unnamed: C4.1, R26.2
unnamed: C5.1, FB1.2, U6.28
unnamed: C8.1, U6.20
unnamed: C15.2, R39.2, R40.1, U8.3
unnamed: C26.2, R45.2, R47.2, U9.3
unnamed: C34.1, U16.10
unnamed: C37.1, FB3.2, U17.6
unnamed: C38.1, U16.23
unnamed: C47.1, U22.42
unnamed: C48.1, C50.1, L3.2, L4.2
unnamed: C53.2, U20.37, X3.1
unnamed: C54.2, U20.36, X3.2
unnamed: D1.1, R11.1
unnamed: D4.2, Q6.3
unnamed: D5.2, R28.2
unnamed: D6.1, D7.2, F1.2
unnamed: D8.1, L1.1, Q11.3
unnamed: D9.1, R42.1, R44.2, U9.1
unnamed: D10.1, L2.1, Q12.3
unnamed: D11.2, R61.1
unnamed: D12.2, R63.1
unnamed: D13.2, R66.1
unnamed: P1.1, R33.2, U6.21
unnamed: Q1.1, R5.2
unnamed: Q2.1, R6.2
unnamed: Q3.1, R10.1
unnamed: Q4.3, R19.2, R20.2
unnamed: Q5.1, R18.1
unnamed: Q5.3, R21.2
unnamed: Q6.1, R21.1, R23.2
unnamed: Q6.2, R23.1, R27.1, U4.2
unnamed: Q7.1, Q8.1, Q9.3, Q10.1, R30.2
unnamed: Q11.1, U8.4
unnamed: Q12.1, U9.4
unnamed: R3.2, R4.2, U1.7
unnamed: R7.1, U1.5
unnamed: R8.1, U1.4
unnamed: R9.1, U1.6
unnamed: R13.1, R16.2, U1.11
unnamed: R15.1, U1.10
unnamed: R20.1, R27.2, U4.1
unnamed: R29.1, U5.8
unnamed: R36.2, SW1.2
unnamed: R37.1, U7.6
unnamed: R38.2, R41.1, SW2.1, U7.5
unnamed: R42.2, U7.2, U7.3
unnamed: R43.2, SW2.2
unnamed: R46.2, U10.6
unnamed: R55.2, U16.24
unnamed: R69.1, U22.18
unnamed: R70.1, U22.17
unnamed: R71.1, U22.19
PDI: PDI1.1, U20.34
PWM/~VPW: Q4.1, U6.3
PWM_RX: R12.2, U1.2, U6.5
SEQ_DM: U16.2, U20.26
SEQ_DP: U16.3, U20.27
SEQ_LED1: D11.1, U20.1, U20.29
SEQ_LED2: D12.1, U20.2, U20.33
SEQ_LED3: D13.1, U20.3, U20.32
SEQ_MISO: U17.12, U20.16
SEQ_MOSI: U17.13, U18.14, U20.15
SEQ_RESET: PDI1.5, U20.35
SEQ_SCK: U17.14, U18.11, U20.17
SEQ_SS: U17.7, U20.14
SEQ_WAKE: U20.20, U22.52
SIMCARD: P24.SW1, U20.25
SIMCARD_CLK: P24.C3, R71.2, U23.1
SIMCARD_DATA: P24.C7, R70.2, U23.3
SIMCARD_RESET: P24.C2, R69.2, U23.6
SIMCARD_V: C49.1, P24.C1, P24.C6, U22.20, U23.4
SIM_DM: U16.4, U22.12
SIM_DP: U16.5, U22.13
SIM_NET: U20.21, U22.51
SIM_PWR_ON: Q15.1, U18.5
SIM_RESET: U18.6, U22.4
SIM_RXD: U20.23, U22.68
SIM_TXD: U20.22, U22.71
SIM_WAKE: U18.7, U22.50
SR_CLEAR: U18.10, U20.10
SR_LATCH: U18.12, U20.11
~CAN_RESET: U6.1, U18.4
~CAN_SLEEP: U6.12, U18.3
~HUB_RESET: R53.2, R54.1, U16.15
~SIM_PWR_ON: Q15.3, R67.1, U22.3
~VPW_RX: R14.2, U1.1, U6.4
